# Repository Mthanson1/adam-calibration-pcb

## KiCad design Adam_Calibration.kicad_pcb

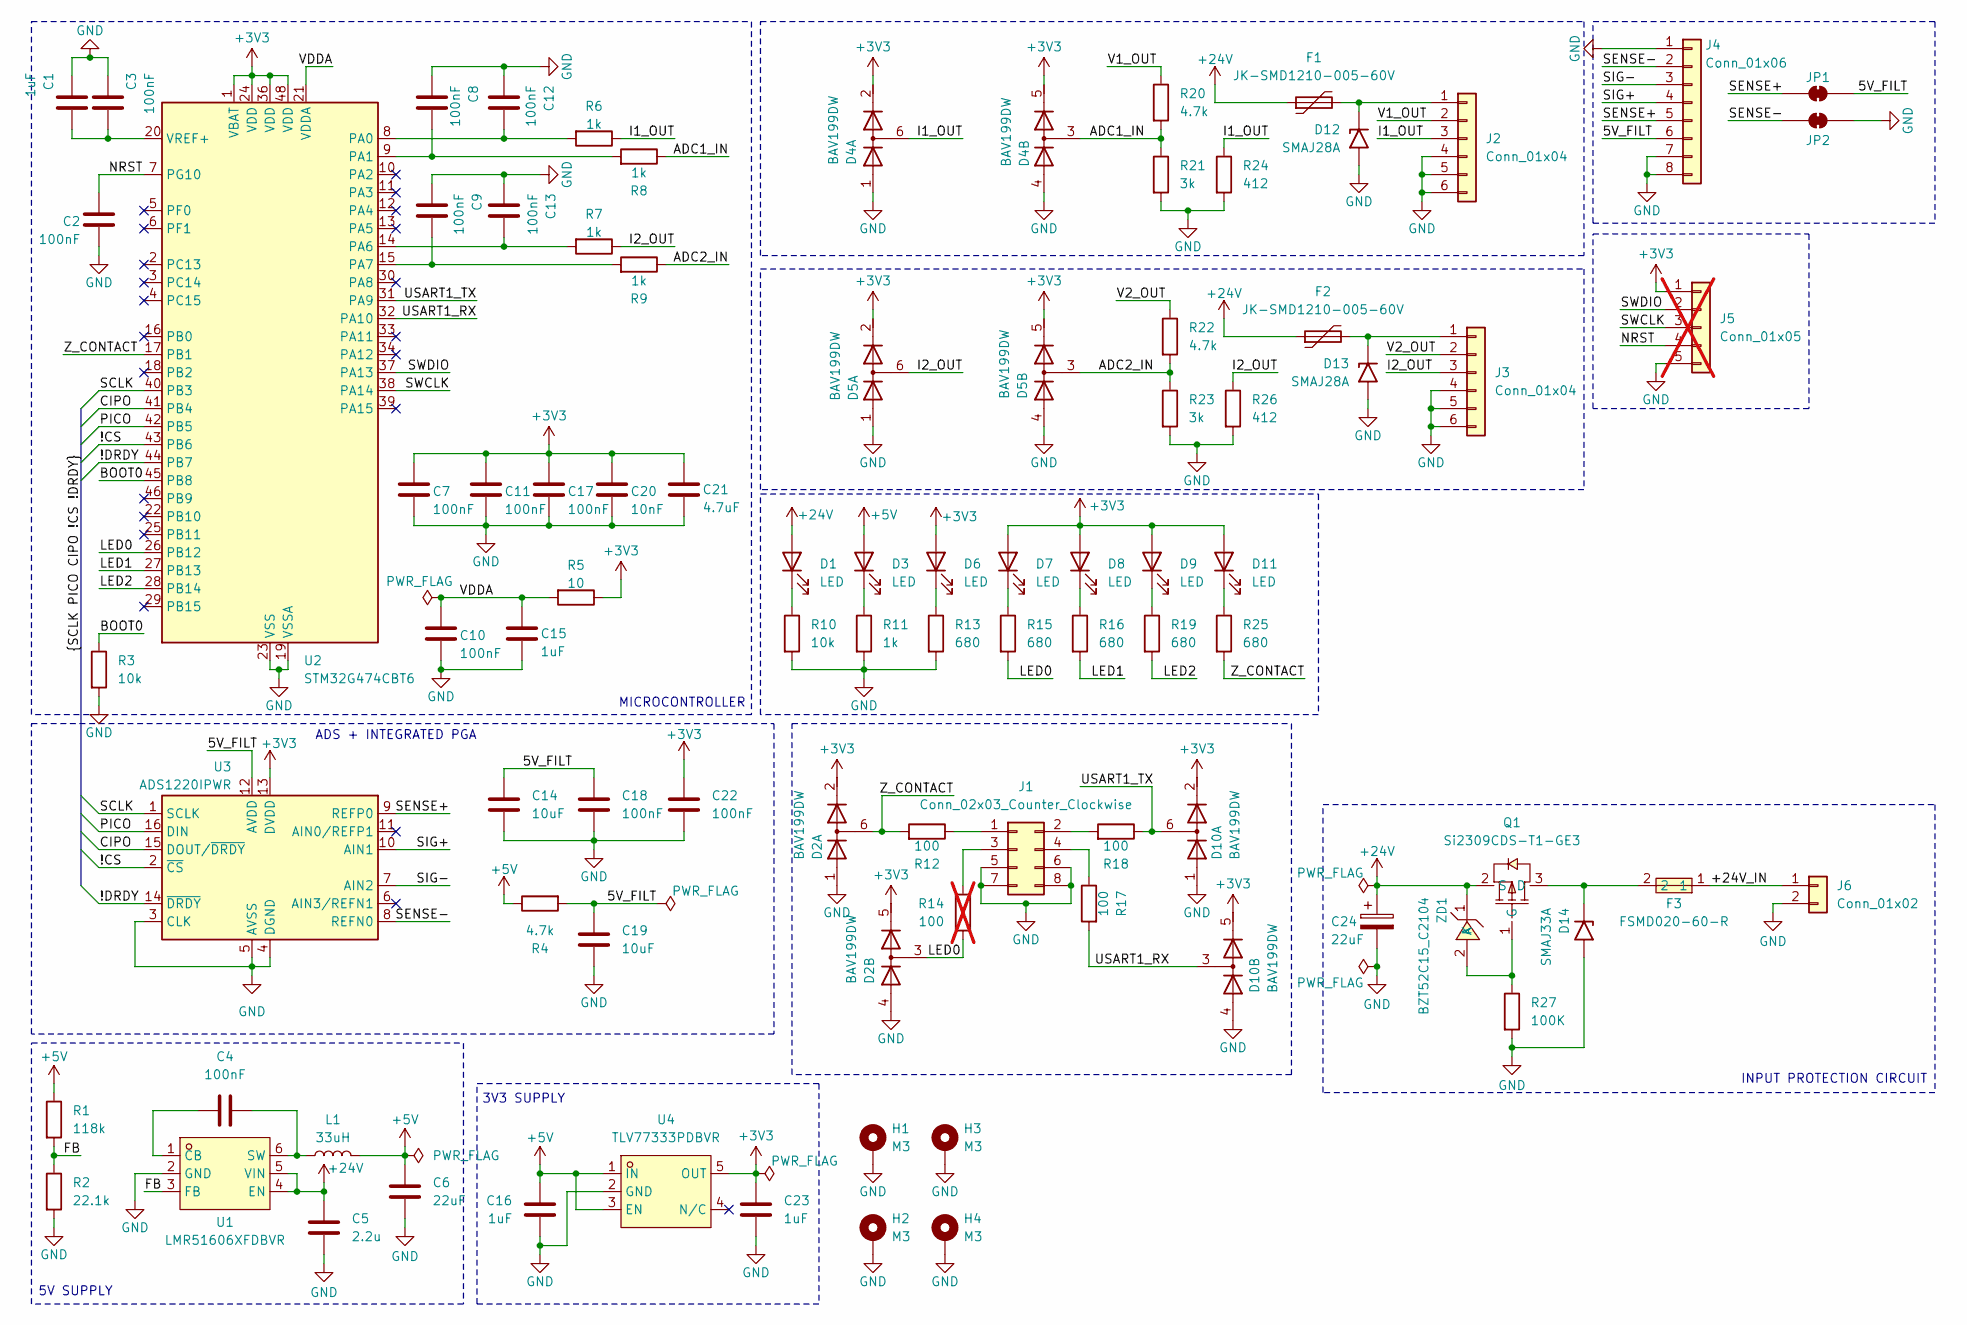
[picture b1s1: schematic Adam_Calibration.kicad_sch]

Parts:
C1, C15, C16, C23: 1uF; C_0603_1608Metric; LCSC C458913
C2, C3, C4, C7, C8, C9, C10, C11, C12, C13, C17, C18, C22: 100nF; C_0603_1608Metric; LCSC C525499
C5: 2.2u; C_1206_3216Metric; LCSC C32071
C6: 22uF; C_1206_3216Metric; LCSC C1849
C14, C19: 10uF; C_0805_2012Metric; LCSC C1713
C20: 10nF; C_0603_1608Metric; LCSC C519509
C21: 4.7uF; C_0805_2012Metric; LCSC C1746
C24: 22uF; CP_Elec_6.3x5.9; LCSC C128458
D1, D3: LED; LED_0603_1608Metric; LCSC C12624
D2, D4, D5, D10: BAV199DW; SOT-363_SC-70-6; LCSC C459846
D6, D7, D8, D9: LED; LED_0603_1608Metric; LCSC C125098
D11: LED; LED_0603_1608Metric; LCSC C2286
D12, D13: SMAJ28A; D_SMA; LCSC C134977
D14: SMAJ33A; D_SMA; LCSC C113966
F1, F2: JK-SMD1210-005-60V; R_1210_3225Metric; LCSC C2835058
F3: FSMD020-60-R; F1812; MPN FSMD020-60-R; LCSC Part C224191
H1, H2, H3, H4: M3; MountingHole_3.2mm_M3_ISO14580_Pad
J1: Conn_02x03_Counter_Clockwise; CONN-SMD_6P-P3.0-H-R2-C3-S4.63; LCSC C587578
J2, J3: Conn_01x04; CONN-SMD_A2501WR-S-4P; LCSC C273222
J4: Conn_01x06; CONN-SMD_A2501WR-S-6P; LCSC C273223
J5: Conn_01x05; PinHeader_1x05_P2.54mm_Vertical; not fitted
J6: Conn_01x02; CONN-SMD_A2501WR-S-2P; LCSC C273220
JP1, JP2: SolderJumper_2_Bridged; SolderJumper-2_P1.3mm_Open_TrianglePad1.0x1.5mm
L1: 33uH; L_Sunlord_SWPA4030S; LCSC C83470
Q1: Si2309CDS-T1-GE3; SOT-23_L2.9-W1.3-P1.90-LS2.4-BR; MPN SI2309CDS-T1-GE3; LCSC Part C10493
R1: 118k; R_0603_1608Metric; LCSC C25806
R2: 22.1k; R_0603_1608Metric; LCSC C25961
R3: 10k; R_0603_1608Metric; LCSC C25804
R4, R20, R22: 4.7k; R_0603_1608Metric; LCSC C23162
R5: 10; R_0603_1608Metric; LCSC C22859
R6, R7, R8, R9, R11: 1k; R_0603_1608Metric; LCSC C21190
R10: 10k; R_0805_2012Metric; LCSC C17414
R12, R17, R18: 100; R_0603_1608Metric; LCSC C22775
R13, R15, R16, R19, R25: 680; R_0603_1608Metric; LCSC C23228
R14: 100; R_0603_1608Metric; LCSC C22775; not fitted
R21, R23: 3k; R_0603_1608Metric; LCSC C4211
R24, R26: 412; R_0603_1608Metric; LCSC C666876
R27: 100K; R_0603_1608Metric; LCSC C14675
U1: LMR51606XFDBVR; SOT-23-6_L2.9-W1.6-P0.95-LS2.8-BR; MPN LMR51606XFDBVR; LCSC Part C22427653
U2: STM32G474CBT6; LQFP-48_7x7mm_P0.5mm; LCSC C730123
U3: ADS1220IPWR; TSSOP-16_4.4x5mm_P0.65mm; LCSC C48263
U4: TLV77333PDBVR; SOT-23-5_L2.9-W1.6-P0.95-LS2.8-BR; MPN TLV77333PDBVR; LCSC Part C32445874
ZD1: BZT52C15_C2104; SOD-123_L2.8-W1.8-LS3.7-RD; MPN BZT52C15; LCSC Part C2104

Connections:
+3V3: C7.1, C11.1, C17.1, C20.1, C21.1, C22.1, C23.1, D2.2 (K2), D2.5 (K4), D4.2 (K2), D4.5 (K4), D5.2 (K2), D5.5 (K4), D6.2 (A), D7.2 (A), D8.2 (A), D9.2 (A), D10.2 (K2), D10.5 (K4), D11.2 (A), J5.1, R5.1, U2.1 (VBAT), U2.24 (VDD), U2.36 (VDD), U2.48 (VDD), U3.13 (DVDD), U4.5 (OUT)
+5V: C6.1, C16.1, D3.2 (A), L1.2, R1.1, R4.1, U4.1 (IN), U4.3 (EN)
+24V: C5.1, C24.1, D1.2 (A), F1.1, F2.1, Q1.2 (S), U1.4 (EN), U1.5 (VIN), ZD1.1 (K)
/5V_FILT: C14.1, C18.1, C19.1, J4.6, JP1.2 (B), R4.2, U3.12 (AVDD)
/!CS: U2.43 (PB6), U3.2 (~CS)
/!DRDY: U2.44 (PB7), U3.14 (~DRDY)
/+24V_IN: F3.1, J6.1
/ADC1_IN: D4.3 (K1A2), R8.1, R20.2, R21.1
/ADC2_IN: D5.3 (K1A2), R9.1, R22.2, R23.1
/BOOT0: R3.1, U2.45 (PB8)
/CIPO: U2.41 (PB4), U3.15 (DOUT/~DRDY)
/FB: R1.2, R2.1, U1.3 (FB)
/I1_OUT: D4.6 (K3A4), J2.3, R6.1, R24.1
/I2_OUT: D5.6 (K3A4), J3.3, R7.1, R26.1
/LED0: D2.3 (K1A2), R14.2, R15.2, U2.26 (PB12)
/LED1: R16.2, U2.27 (PB13)
/LED2: R19.2, U2.28 (PB14)
/NRST: C2.1, J5.4, U2.7 (PG10)
/PICO: U2.42 (PB5), U3.16 (DIN)
/SCLK: U2.40 (PB3), U3.1 (SCLK)
/SENSE+: J4.5, JP1.1 (A), U3.9 (REFP0)
/SENSE-: J4.2, JP2.1 (A), U3.8 (REFN0)
/SIG+: J4.4, U3.10 (AIN1)
/SIG-: J4.3, U3.7 (AIN2)
/SWCLK: J5.3, U2.38 (PA14)
/SWDIO: J5.2, U2.37 (PA13)
/USART1_RX: D10.3 (K1A2), R17.2, U2.32 (PA10)
/USART1_TX: D10.6 (K3A4), R18.1, U2.31 (PA9)
/V1_OUT: J2.2, R20.1
/V2_OUT: J3.2, R22.1
/VDDA: C10.1, C15.1, R5.2, U2.21 (VDDA)
/Z_CONTACT: D2.6 (K3A4), R12.2, R25.2, U2.17 (PB1)
GND: C1.1, C2.2, C3.1, C5.2, C6.2, C7.2, C8.1, C9.1, C10.2, C11.2, C12.1, C13.1, C14.2, C15.2, C16.2, C17.2, C18.2, C19.2, C20.2, C21.2, C22.2, C23.2, C24.2, D2.1 (A1), D2.4 (A3), D4.1 (A1), D4.4 (A3), D5.1 (A1), D5.4 (A3), D10.1 (A1), D10.4 (A3), D12.2 (A2), D13.2 (A2), D14.2 (A2), H1.1 (1_1), H2.1 (1_1), H3.1 (1_1), H4.1 (1_1), J1.5, J1.6, J1.7, J1.8, J2.4, J2.5, J2.6, J3.4, J3.5, J3.6, J4.1, J4.7, J4.8, J5.5, J6.2, JP2.2 (B), R2.2, R3.2, R10.2, R11.2, R13.2, R21.2, R23.2, R24.2, R26.2, R27.2, U1.2 (GND), U2.19 (VSSA), U2.23 (VSS), U2.35 (VSS), U2.47 (VSS), U3.3 (CLK), U3.4 (DGND), U3.5 (AVSS), U4.2 (GND)
unnamed: D1.1 (K), R10.1
unnamed: D3.1 (K), R11.1
unnamed: D6.1 (K), R13.1
unnamed: D7.1 (K), R15.1
unnamed: D8.1 (K), R16.1
unnamed: D9.1 (K), R19.1
unnamed: D11.1 (K), R25.1
unnamed: D12.1 (A1), F1.2, J2.1
unnamed: D13.1 (A1), F2.2, J3.1
unnamed: D14.1 (A1), F3.2, Q1.3 (D)
unnamed: J1.1, R12.1
unnamed: J1.2, R18.2
unnamed: J1.3, R14.1
unnamed: J1.4, R17.1
unnamed: Q1.1 (G), R27.1, ZD1.2 (A)
unnamed: C4.1, U1.1 (CB)
unnamed: C4.2, L1.1, U1.6 (SW)
unnamed: C12.2, R6.2, U2.8 (PA0)
unnamed: C8.2, R8.2, U2.9 (PA1)
unnamed: C13.2, R7.2, U2.14 (PA6)
unnamed: C9.2, R9.2, U2.15 (PA7)
unnamed: C1.2, C3.2, U2.20 (VREF+)

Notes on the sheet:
5V SUPPLY
ADS + INTEGRATED PGA
INPUT PROTECTION CIRCUIT
3V3 SUPPLY
MICROCONTROLLER

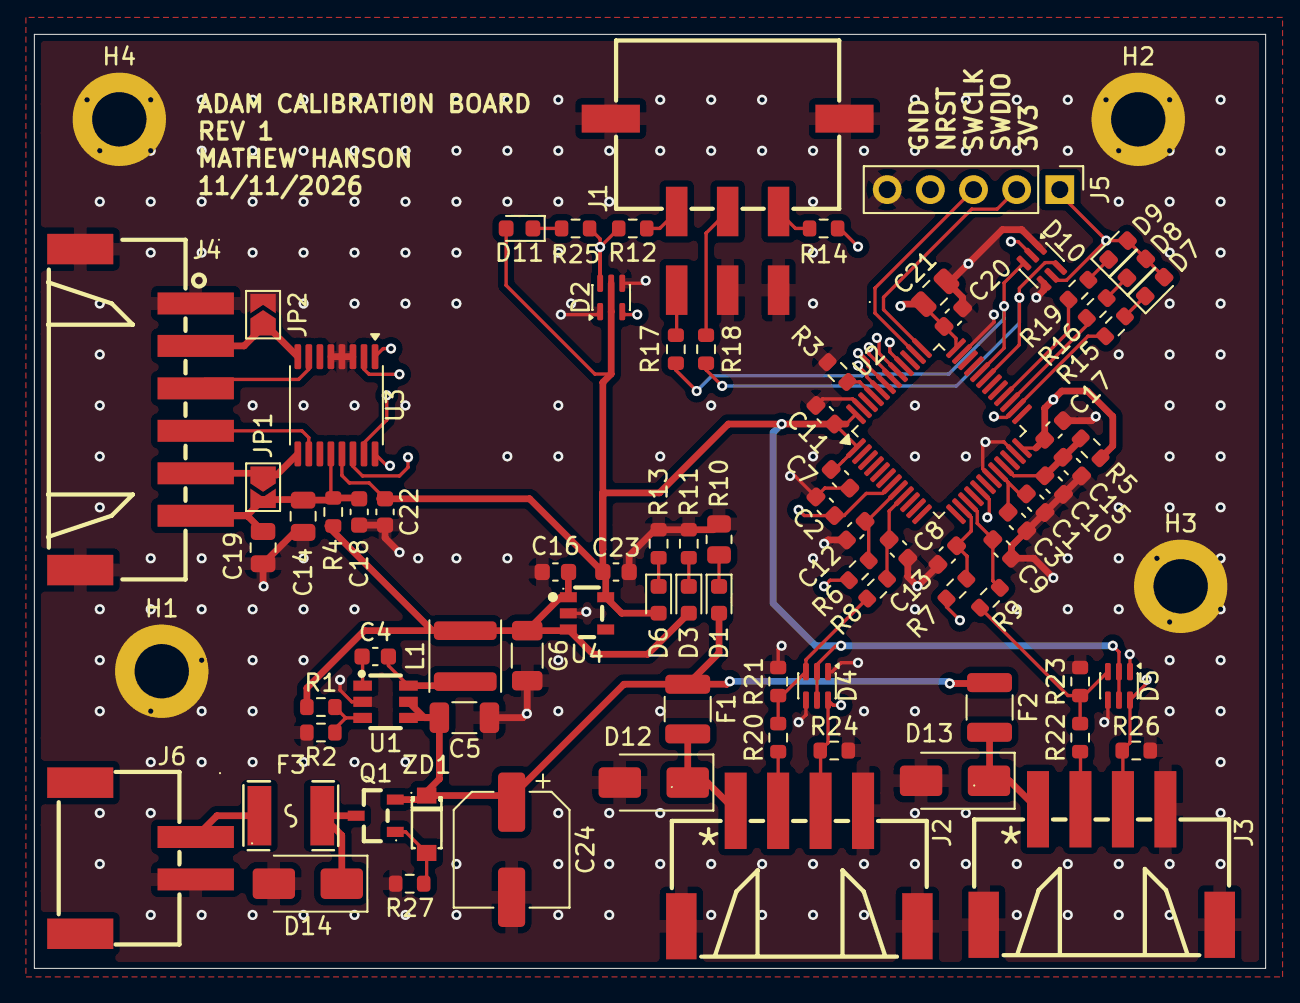
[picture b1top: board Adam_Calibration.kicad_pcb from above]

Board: 4 copper layers, 72.5 x 55.0 mm, 87 parts (0 on the bottom side), 55 nets.

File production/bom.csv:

Designator,Footprint,Quantity,Value,LCSC Part #
"C1, C15, C16, C23",0603,4,1uF,C458913
"C10, C11, C12, C13, C17, C18, C2, C22, C3, C4, C7, C8, C9",0603,13,100nF,C525499
"C14, C19",0805,2,10uF,C1713
C20,0603,1,10nF,C519509
C21,0805,1,4.7uF,C1746
C24,CP_Elec_6.3x5.9,1,22uF,C128458
C5,1206,1,2.2u,C32071
C6,1206,1,22uF,C1849
"D1, D3",0603,2,LED,C12624
"D10, D2, D4, D5",SOT-363_SC-70-6,4,BAV199DW,C459846
D11,0603,1,LED,C2286
"D12, D13",D_SMA,2,SMAJ28A,C134977
D14,D_SMA,1,SMAJ33A,C113966
"D6, D7, D8, D9",0603,4,LED,C125098
"F1, F2",1210,2,JK-SMD1210-005-60V,C2835058
F3,F1812,1,FSMD020-60-R,C224191
J1,CONN-SMD_6P-P3.0-H-R2-C3-S4.63,1,Conn_02x03_Counter_Clockwise,C587578
"J2, J3",CONN-SMD_A2501WR-S-4P,2,Conn_01x04,C273222
J4,CONN-SMD_A2501WR-S-6P,1,Conn_01x06,C273223
J6,CONN-SMD_A2501WR-S-2P,1,Conn_01x02,C273220
L1,L_Sunlord_SWPA4030S,1,33uH,C83470
Q1,SOT-23_L2.9-W1.3-P1.90-LS2.4-BR,1,Si2309CDS-T1-GE3,C10493
R1,0603,1,118k,C25806
R10,0805,1,10k,C17414
"R11, R6, R7, R8, R9",0603,5,1k,C21190
"R12, R17, R18",0603,3,100,C22775
"R13, R15, R16, R19, R25",0603,5,680,C23228
R2,0603,1,22.1k,C25961
"R20, R22, R4",0603,3,4.7k,C23162
"R21, R23",0603,2,3k,C4211
"R24, R26",0603,2,412,C666876
R27,0603,1,100K,C14675
R3,0603,1,10k,C25804
R5,0603,1,10,C22859
U1,SOT-23-6_L2.9-W1.6-P0.95-LS2.8-BR,1,LMR51606XFDBVR,C22427653
U2,LQFP-48_7x7mm_P0.5mm,1,STM32G474CBT6,C730123
U3,TSSOP-16_4.4x5mm_P0.65mm,1,ADS1220IPWR,C48263
U4,SOT-23-5_L2.9-W1.6-P0.95-LS2.8-BR,1,TLV77333PDBVR,C32445874
ZD1,SOD-123_L2.8-W1.8-LS3.7-RD,1,BZT52C15_C2104,C2104
